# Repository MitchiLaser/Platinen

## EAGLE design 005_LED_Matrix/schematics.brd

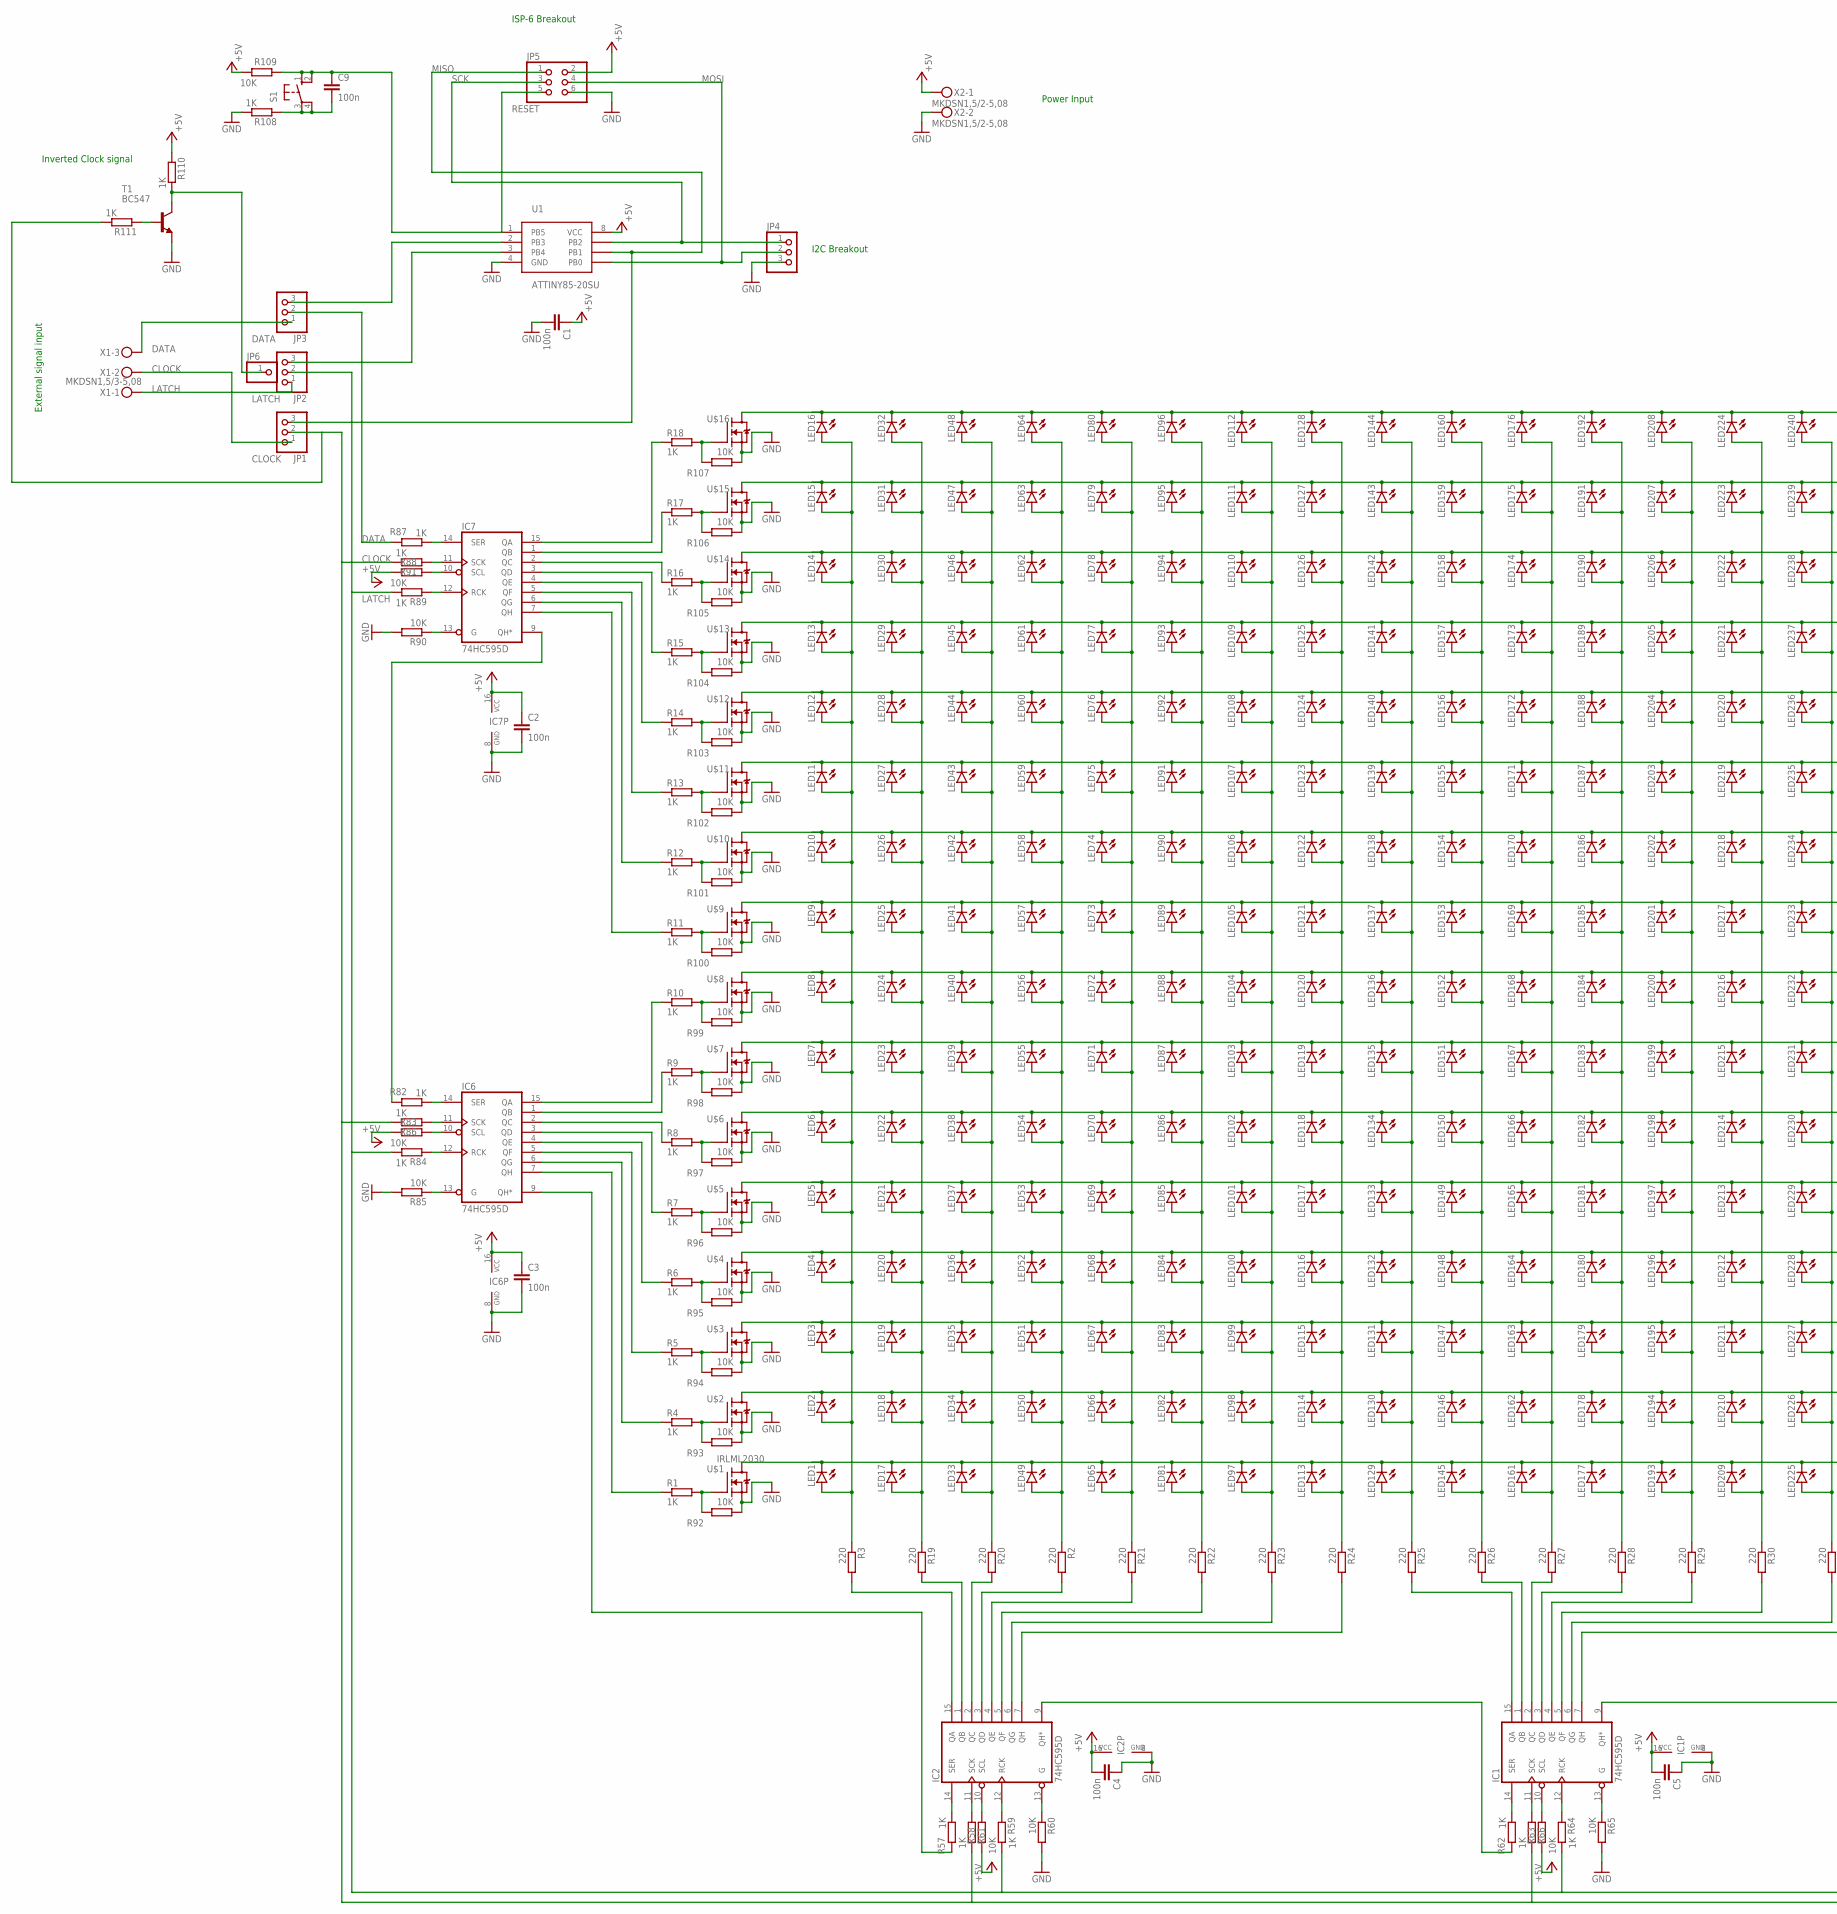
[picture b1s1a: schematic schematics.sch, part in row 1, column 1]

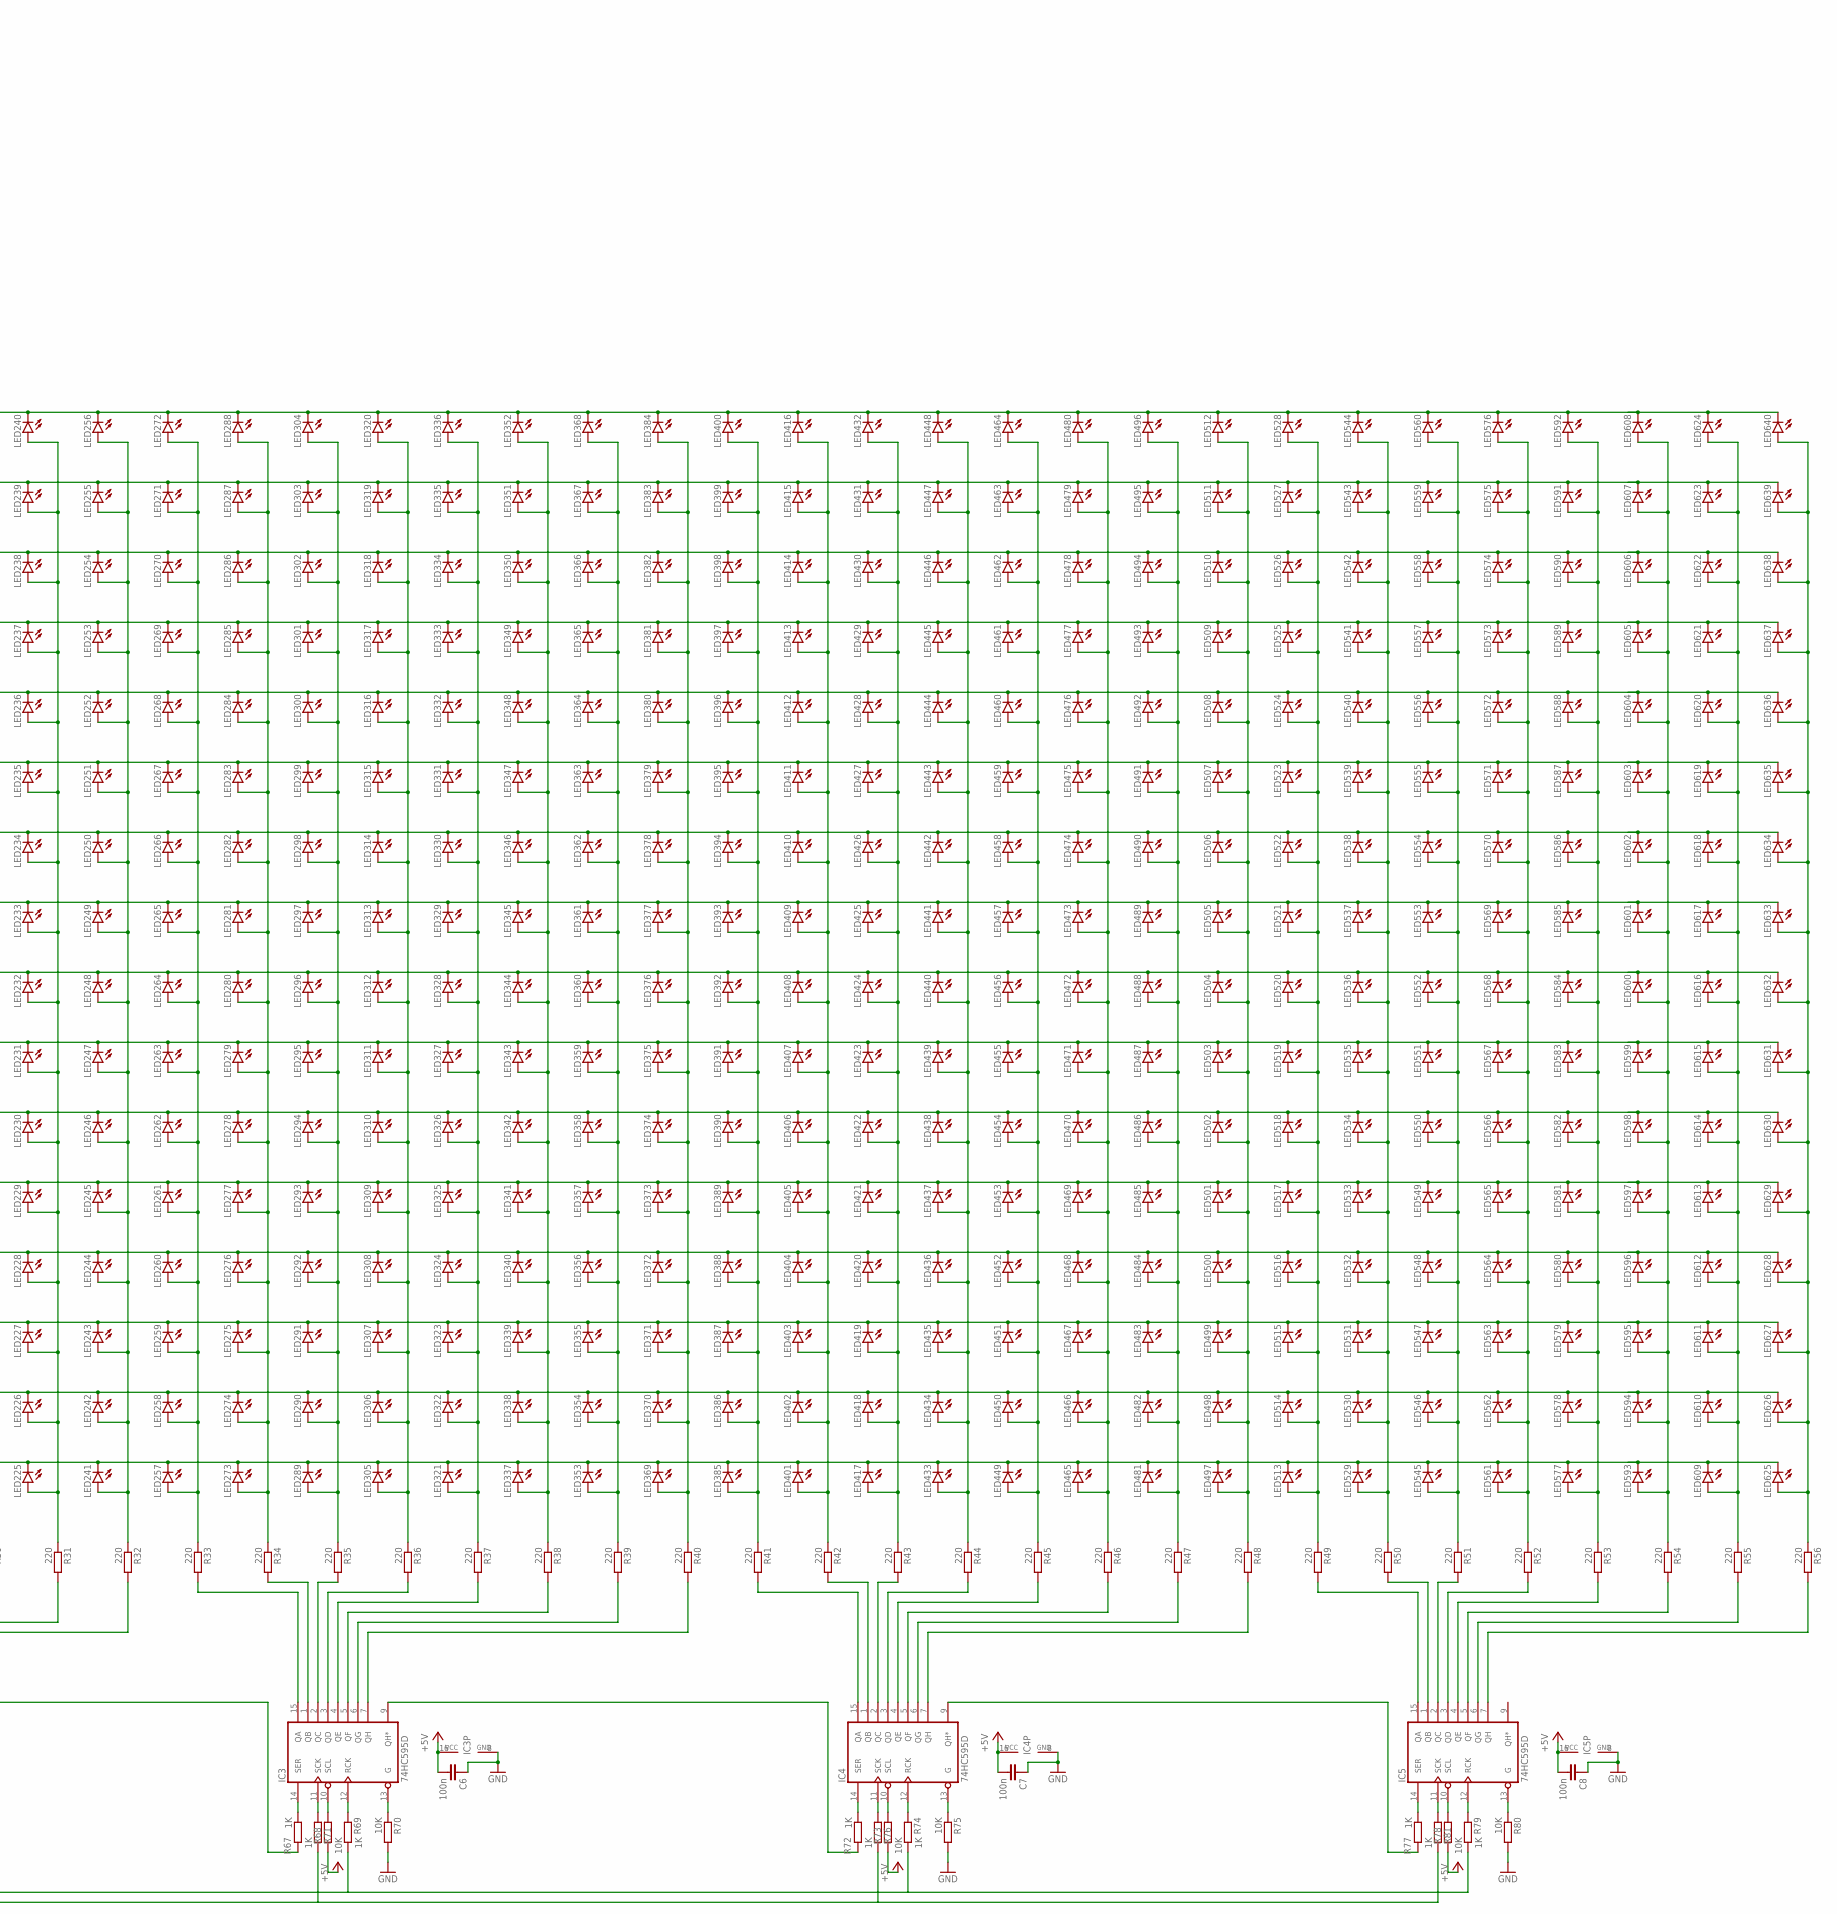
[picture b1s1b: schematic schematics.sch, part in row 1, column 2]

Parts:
C1, C2, C3, C4, C5, C6, C7, C8, C9: 100n; C0805K
IC1, IC2, IC3, IC4, IC5, IC6, IC7: 74HC595D; SO16
JP1, JP2, JP3, JP4: PINHD-1X3; 1X03
JP5: PINHD-2X3; 2X03
JP6: PINHD-1X1; 1X01
LED1, LED2, LED3, LED4, LED5, LED6, LED7, LED8, LED9, LED10, LED11, LED12, LED13, LED14, LED15, LED16, LED17, LED18, LED19, LED20, LED21, LED22, LED23, LED24, LED25, LED26, LED27, LED28, LED29, LED30, LED31, LED32, LED33, LED34, LED35, LED36, LED37, LED38, LED39, LED40, LED41, LED42, LED43, LED44, LED45, LED46, LED47, LED48, LED49, LED50, LED51, LED52, LED53, LED54, LED55, LED56, LED57, LED58, LED59, LED60, LED61, LED62, LED63, LED64, LED65, LED66, LED67, LED68, LED69, LED70, LED71, LED72, LED73, LED74, LED75, LED76, LED77, LED78, LED79, LED80, LED81, LED82, LED83, LED84, LED85, LED86, LED87, LED88, LED89, LED90, LED91, LED92, LED93, LED94, LED95, LED96, LED97, LED98, LED99, LED100, LED101, LED102, LED103, LED104, LED105, LED106, LED107, LED108, LED109, LED110, LED111, LED112, LED113, LED114, LED115, LED116, LED117, LED118, LED119, LED120, LED121, LED122, LED123, LED124, LED125, LED126, LED127, LED128, LED129, LED130, LED131, LED132, LED133, LED134, LED135, LED136, LED137, LED138, LED139, LED140, LED141, LED142, LED143, LED144, LED145, LED146, LED147, LED148, LED149, LED150, LED151, LED152, LED153, LED154, LED155, LED156, LED157, LED158, LED159, LED160, LED161, LED162, LED163, LED164, LED165, LED166, LED167, LED168, LED169, LED170, LED171, LED172, LED173, LED174, LED175, LED176, LED177, LED178, LED179, LED180, LED181, LED182, LED183, LED184, LED185, LED186, LED187, LED188, LED189, LED190, LED191, LED192, LED193, LED194, LED195, LED196, LED197, LED198, LED199, LED200, LED201, LED202, LED203, LED204, LED205, LED206, LED207, LED208, LED209, LED210, LED211, LED212, LED213, LED214, LED215, LED216, LED217, LED218, LED219, LED220, LED221, LED222, LED223, LED224, LED225, LED226, LED227, LED228, LED229, LED230, LED231, LED232, LED233, LED234, LED235, LED236, LED237, LED238, LED239, LED240, LED241, LED242, LED243, LED244, LED245, LED246, LED247, LED248, LED249, LED250, LED251, LED252, LED253, LED254, LED255, LED256, LED257, LED258, LED259, LED260, LED261, LED262, LED263, LED264, LED265, LED266, LED267, LED268, LED269, LED270, LED271, LED272, LED273, LED274, LED275, LED276, LED277, LED278, LED279, LED280, LED281, LED282, LED283, LED284, LED285, LED286, LED287, LED288, LED289, LED290, LED291, LED292, LED293, LED294, LED295, LED296, LED297, LED298, LED299, LED300, LED301, LED302, LED303, LED304, LED305, LED306, LED307, LED308, LED309, LED310, LED311, LED312, LED313, LED314, LED315, LED316, LED317, LED318, LED319, LED320, LED321, LED322, LED323, LED324, LED325, LED326, LED327, LED328, LED329, LED330, LED331, LED332, LED333, LED334, LED335, LED336, LED337, LED338, LED339, LED340, LED341, LED342, LED343, LED344, LED345, LED346, LED347, LED348, LED349, LED350, LED351, LED352, LED353, LED354, LED355, LED356, LED357, LED358, LED359, LED360, LED361, LED362, LED363, LED364, LED365, LED366, LED367, LED368, LED369, LED370, LED371, LED372, LED373, LED374, LED375, LED376, LED377, LED378, LED379, LED380, LED381, LED382, LED383, LED384, LED385, LED386, LED387, LED388, LED389, LED390, LED391, LED392, LED393, LED394, LED395, LED396, LED397, LED398, LED399, LED400, LED401, LED402, LED403, LED404, LED405, LED406, LED407, LED408, LED409, LED410, LED411, LED412, LED413, LED414, LED415, LED416, LED417, LED418, LED419, LED420, LED421, LED422, LED423, LED424, LED425, LED426, LED427, LED428, LED429, LED430, LED431, LED432, LED433, LED434, LED435, LED436, LED437, LED438, LED439, LED440, LED441, LED442, LED443, LED444, LED445, LED446, LED447, LED448, LED449, LED450, LED451, LED452, LED453, LED454, LED455, LED456, LED457, LED458, LED459, LED460, LED461, LED462, LED463, LED464, LED465, LED466, LED467, LED468, LED469, LED470, LED471, LED472, LED473, LED474, LED475, LED476, LED477, LED478, LED479, LED480, LED481, LED482, LED483, LED484, LED485, LED486, LED487, LED488, LED489, LED490, LED491, LED492, LED493, LED494, LED495, LED496, LED497, LED498, LED499, LED500, LED501, LED502, LED503, LED504, LED505, LED506, LED507, LED508, LED509, LED510, LED511, LED512, LED513, LED514, LED515, LED516, LED517, LED518, LED519, LED520, LED521, LED522, LED523, LED524, LED525, LED526, LED527, LED528, LED529, LED530, LED531, LED532, LED533, LED534, LED535, LED536, LED537, LED538, LED539, LED540, LED541, LED542, LED543, LED544, LED545, LED546, LED547, LED548, LED549, LED550, LED551, LED552, LED553, LED554, LED555, LED556, LED557, LED558, LED559, LED560, LED561, LED562, LED563, LED564, LED565, LED566, LED567, LED568, LED569, LED570, LED571, LED572, LED573, LED574, LED575, LED576, LED577, LED578, LED579, LED580, LED581, LED582, LED583, LED584, LED585, LED586, LED587, LED588, LED589, LED590, LED591, LED592, LED593, LED594, LED595, LED596, LED597, LED598, LED599, LED600, LED601, LED602, LED603, LED604, LED605, LED606, LED607, LED608, LED609, LED610, LED611, LED612, LED613, LED614, LED615, LED616, LED617, LED618, LED619, LED620, LED621, LED622, LED623, LED624, LED625, LED626, LED627, LED628, LED629, LED630, LED631, LED632, LED633, LED634, LED635, LED636, LED637, LED638, LED639, LED640: LED3MM
R1, R4, R5, R6, R7, R8, R9, R10, R11, R12, R13, R14, R15, R16, R17, R18, R57, R58, R59, R62, R63, R64, R67, R68, R69, R72, R73, R74, R77, R78, R79, R82, R83, R84, R87, R88, R89, R108, R110, R111: 1K; R0805W
R2, R3, R19, R20, R21, R22, R23, R24, R25, R26, R27, R28, R29, R30, R31, R32, R33, R34, R35, R36, R37, R38, R39, R40, R41, R42, R43, R44, R45, R46, R47, R48, R49, R50, R51, R52, R53, R54, R55, R56: 220; R0805W
R60, R61, R65, R66, R70, R71, R75, R76, R80, R81, R85, R86, R90, R91, R92, R93, R94, R95, R96, R97, R98, R99, R100, R101, R102, R103, R104, R105, R106, R107, R109: 10K; R0805W
S1: 10-XX; B3F-10XX
T1: BC547; TO92
U1: ATTINY85-20SU; SOIC-8
U$1, U$2, U$3, U$4, U$5, U$6, U$7, U$8, U$9, U$10, U$11, U$12, U$13, U$14, U$15, U$16: IRLML2030; SOT23
X1: MKDSN1,5/3-5,08
X2: MKDSN1,5/2-5,08

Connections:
+5V: C1.1, C2.1, C3.1, C4.2, C5.2, C6.2, C7.2, C8.2, IC1.16 (VCC), IC2.16 (VCC), IC3.16 (VCC), IC4.16 (VCC), IC5.16 (VCC), IC6.16 (VCC), IC7.16 (VCC), JP5.2, R61.2, R66.2, R71.2, R76.2, R81.2, R86.2, R91.2, R109.2, R110.1, U1.8 (VCC), X2.1
CLOCK: JP1.2, R58.2, R63.2, R68.2, R73.2, R78.2, R83.2, R88.2, R111.2
DATA: JP3.2, R87.2
GND: C1.2, C2.2, C3.2, C4.1, C5.1, C6.1, C7.1, C8.1, IC1.8 (GND), IC2.8 (GND), IC3.8 (GND), IC4.8 (GND), IC5.8 (GND), IC6.8 (GND), IC7.8 (GND), JP4.3, JP5.6, R60.2, R65.2, R70.2, R75.2, R80.2, R85.2, R90.2, R92.2, R93.2, R94.2, R95.2, R96.2, R97.2, R98.2, R99.2, R100.2, R101.2, R102.2, R103.2, R104.2, R105.2, R106.2, R107.2, R108.2, T1.1 (E), U1.4 (GND), U$1.2 (S), U$2.2 (S), U$3.2 (S), U$4.2 (S), U$5.2 (S), U$6.2 (S), U$7.2 (S), U$8.2 (S), U$9.2 (S), U$10.2 (S), U$11.2 (S), U$12.2 (S), U$13.2 (S), U$14.2 (S), U$15.2 (S), U$16.2 (S), X2.2
LATCH: JP2.2, R59.2, R64.2, R69.2, R74.2, R79.2, R84.2, R89.2
MISO: JP1.3, JP5.1, U1.6 (PB1)
MOSI: JP4.2, JP5.4, U1.5 (PB0)
unnamed: LED1.A, LED2.A, LED3.A, LED4.A, LED5.A, LED6.A, LED7.A, LED8.A, LED9.A, LED10.A, LED11.A, LED12.A, LED13.A, LED14.A, LED15.A, LED16.A, R3.1
unnamed: LED2.K (C), LED18.K (C), LED34.K (C), LED50.K (C), LED66.K (C), LED82.K (C), LED98.K (C), LED114.K (C), LED130.K (C), LED146.K (C), LED162.K (C), LED178.K (C), LED194.K (C), LED210.K (C), LED226.K (C), LED242.K (C), LED258.K (C), LED274.K (C), LED290.K (C), LED306.K (C), LED322.K (C), LED338.K (C), LED354.K (C), LED370.K (C), LED386.K (C), LED402.K (C), LED418.K (C), LED434.K (C), LED450.K (C), LED466.K (C), LED482.K (C), LED498.K (C), LED514.K (C), LED530.K (C), LED546.K (C), LED562.K (C), LED578.K (C), LED594.K (C), LED610.K (C), LED626.K (C), U$2.3 (D)
unnamed: R4.2, R93.1, U$2.1 (G)
unnamed: LED3.K (C), LED19.K (C), LED35.K (C), LED51.K (C), LED67.K (C), LED83.K (C), LED99.K (C), LED115.K (C), LED131.K (C), LED147.K (C), LED163.K (C), LED179.K (C), LED195.K (C), LED211.K (C), LED227.K (C), LED243.K (C), LED259.K (C), LED275.K (C), LED291.K (C), LED307.K (C), LED323.K (C), LED339.K (C), LED355.K (C), LED371.K (C), LED387.K (C), LED403.K (C), LED419.K (C), LED435.K (C), LED451.K (C), LED467.K (C), LED483.K (C), LED499.K (C), LED515.K (C), LED531.K (C), LED547.K (C), LED563.K (C), LED579.K (C), LED595.K (C), LED611.K (C), LED627.K (C), U$3.3 (D)
unnamed: R5.2, R94.1, U$3.1 (G)
unnamed: LED4.K (C), LED20.K (C), LED36.K (C), LED52.K (C), LED68.K (C), LED84.K (C), LED100.K (C), LED116.K (C), LED132.K (C), LED148.K (C), LED164.K (C), LED180.K (C), LED196.K (C), LED212.K (C), LED228.K (C), LED244.K (C), LED260.K (C), LED276.K (C), LED292.K (C), LED308.K (C), LED324.K (C), LED340.K (C), LED356.K (C), LED372.K (C), LED388.K (C), LED404.K (C), LED420.K (C), LED436.K (C), LED452.K (C), LED468.K (C), LED484.K (C), LED500.K (C), LED516.K (C), LED532.K (C), LED548.K (C), LED564.K (C), LED580.K (C), LED596.K (C), LED612.K (C), LED628.K (C), U$4.3 (D)
unnamed: R6.2, R95.1, U$4.1 (G)
unnamed: LED5.K (C), LED21.K (C), LED37.K (C), LED53.K (C), LED69.K (C), LED85.K (C), LED101.K (C), LED117.K (C), LED133.K (C), LED149.K (C), LED165.K (C), LED181.K (C), LED197.K (C), LED213.K (C), LED229.K (C), LED245.K (C), LED261.K (C), LED277.K (C), LED293.K (C), LED309.K (C), LED325.K (C), LED341.K (C), LED357.K (C), LED373.K (C), LED389.K (C), LED405.K (C), LED421.K (C), LED437.K (C), LED453.K (C), LED469.K (C), LED485.K (C), LED501.K (C), LED517.K (C), LED533.K (C), LED549.K (C), LED565.K (C), LED581.K (C), LED597.K (C), LED613.K (C), LED629.K (C), U$5.3 (D)
unnamed: R7.2, R96.1, U$5.1 (G)
unnamed: LED6.K (C), LED22.K (C), LED38.K (C), LED54.K (C), LED70.K (C), LED86.K (C), LED102.K (C), LED118.K (C), LED134.K (C), LED150.K (C), LED166.K (C), LED182.K (C), LED198.K (C), LED214.K (C), LED230.K (C), LED246.K (C), LED262.K (C), LED278.K (C), LED294.K (C), LED310.K (C), LED326.K (C), LED342.K (C), LED358.K (C), LED374.K (C), LED390.K (C), LED406.K (C), LED422.K (C), LED438.K (C), LED454.K (C), LED470.K (C), LED486.K (C), LED502.K (C), LED518.K (C), LED534.K (C), LED550.K (C), LED566.K (C), LED582.K (C), LED598.K (C), LED614.K (C), LED630.K (C), U$6.3 (D)
unnamed: R8.2, R97.1, U$6.1 (G)
unnamed: LED7.K (C), LED23.K (C), LED39.K (C), LED55.K (C), LED71.K (C), LED87.K (C), LED103.K (C), LED119.K (C), LED135.K (C), LED151.K (C), LED167.K (C), LED183.K (C), LED199.K (C), LED215.K (C), LED231.K (C), LED247.K (C), LED263.K (C), LED279.K (C), LED295.K (C), LED311.K (C), LED327.K (C), LED343.K (C), LED359.K (C), LED375.K (C), LED391.K (C), LED407.K (C), LED423.K (C), LED439.K (C), LED455.K (C), LED471.K (C), LED487.K (C), LED503.K (C), LED519.K (C), LED535.K (C), LED551.K (C), LED567.K (C), LED583.K (C), LED599.K (C), LED615.K (C), LED631.K (C), U$7.3 (D)
unnamed: R9.2, R98.1, U$7.1 (G)
unnamed: LED8.K (C), LED24.K (C), LED40.K (C), LED56.K (C), LED72.K (C), LED88.K (C), LED104.K (C), LED120.K (C), LED136.K (C), LED152.K (C), LED168.K (C), LED184.K (C), LED200.K (C), LED216.K (C), LED232.K (C), LED248.K (C), LED264.K (C), LED280.K (C), LED296.K (C), LED312.K (C), LED328.K (C), LED344.K (C), LED360.K (C), LED376.K (C), LED392.K (C), LED408.K (C), LED424.K (C), LED440.K (C), LED456.K (C), LED472.K (C), LED488.K (C), LED504.K (C), LED520.K (C), LED536.K (C), LED552.K (C), LED568.K (C), LED584.K (C), LED600.K (C), LED616.K (C), LED632.K (C), U$8.3 (D)
unnamed: R10.2, R99.1, U$8.1 (G)
unnamed: LED1.K (C), LED17.K (C), LED33.K (C), LED49.K (C), LED65.K (C), LED81.K (C), LED97.K (C), LED113.K (C), LED129.K (C), LED145.K (C), LED161.K (C), LED177.K (C), LED193.K (C), LED209.K (C), LED225.K (C), LED241.K (C), LED257.K (C), LED273.K (C), LED289.K (C), LED305.K (C), LED321.K (C), LED337.K (C), LED353.K (C), LED369.K (C), LED385.K (C), LED401.K (C), LED417.K (C), LED433.K (C), LED449.K (C), LED465.K (C), LED481.K (C), LED497.K (C), LED513.K (C), LED529.K (C), LED545.K (C), LED561.K (C), LED577.K (C), LED593.K (C), LED609.K (C), LED625.K (C), U$1.3 (D)
unnamed: R1.2, R92.1, U$1.1 (G)
unnamed: LED9.K (C), LED25.K (C), LED41.K (C), LED57.K (C), LED73.K (C), LED89.K (C), LED105.K (C), LED121.K (C), LED137.K (C), LED153.K (C), LED169.K (C), LED185.K (C), LED201.K (C), LED217.K (C), LED233.K (C), LED249.K (C), LED265.K (C), LED281.K (C), LED297.K (C), LED313.K (C), LED329.K (C), LED345.K (C), LED361.K (C), LED377.K (C), LED393.K (C), LED409.K (C), LED425.K (C), LED441.K (C), LED457.K (C), LED473.K (C), LED489.K (C), LED505.K (C), LED521.K (C), LED537.K (C), LED553.K (C), LED569.K (C), LED585.K (C), LED601.K (C), LED617.K (C), LED633.K (C), U$9.3 (D)
unnamed: R11.2, R100.1, U$9.1 (G)
unnamed: LED10.K (C), LED26.K (C), LED42.K (C), LED58.K (C), LED74.K (C), LED90.K (C), LED106.K (C), LED122.K (C), LED138.K (C), LED154.K (C), LED170.K (C), LED186.K (C), LED202.K (C), LED218.K (C), LED234.K (C), LED250.K (C), LED266.K (C), LED282.K (C), LED298.K (C), LED314.K (C), LED330.K (C), LED346.K (C), LED362.K (C), LED378.K (C), LED394.K (C), LED410.K (C), LED426.K (C), LED442.K (C), LED458.K (C), LED474.K (C), LED490.K (C), LED506.K (C), LED522.K (C), LED538.K (C), LED554.K (C), LED570.K (C), LED586.K (C), LED602.K (C), LED618.K (C), LED634.K (C), U$10.3 (D)
unnamed: R12.2, R101.1, U$10.1 (G)
unnamed: LED11.K (C), LED27.K (C), LED43.K (C), LED59.K (C), LED75.K (C), LED91.K (C), LED107.K (C), LED123.K (C), LED139.K (C), LED155.K (C), LED171.K (C), LED187.K (C), LED203.K (C), LED219.K (C), LED235.K (C), LED251.K (C), LED267.K (C), LED283.K (C), LED299.K (C), LED315.K (C), LED331.K (C), LED347.K (C), LED363.K (C), LED379.K (C), LED395.K (C), LED411.K (C), LED427.K (C), LED443.K (C), LED459.K (C), LED475.K (C), LED491.K (C), LED507.K (C), LED523.K (C), LED539.K (C), LED555.K (C), LED571.K (C), LED587.K (C), LED603.K (C), LED619.K (C), LED635.K (C), U$11.3 (D)
unnamed: R13.2, R102.1, U$11.1 (G)
unnamed: LED12.K (C), LED28.K (C), LED44.K (C), LED60.K (C), LED76.K (C), LED92.K (C), LED108.K (C), LED124.K (C), LED140.K (C), LED156.K (C), LED172.K (C), LED188.K (C), LED204.K (C), LED220.K (C), LED236.K (C), LED252.K (C), LED268.K (C), LED284.K (C), LED300.K (C), LED316.K (C), LED332.K (C), LED348.K (C), LED364.K (C), LED380.K (C), LED396.K (C), LED412.K (C), LED428.K (C), LED444.K (C), LED460.K (C), LED476.K (C), LED492.K (C), LED508.K (C), LED524.K (C), LED540.K (C), LED556.K (C), LED572.K (C), LED588.K (C), LED604.K (C), LED620.K (C), LED636.K (C), U$12.3 (D)
unnamed: R14.2, R103.1, U$12.1 (G)
unnamed: LED13.K (C), LED29.K (C), LED45.K (C), LED61.K (C), LED77.K (C), LED93.K (C), LED109.K (C), LED125.K (C), LED141.K (C), LED157.K (C), LED173.K (C), LED189.K (C), LED205.K (C), LED221.K (C), LED237.K (C), LED253.K (C), LED269.K (C), LED285.K (C), LED301.K (C), LED317.K (C), LED333.K (C), LED349.K (C), LED365.K (C), LED381.K (C), LED397.K (C), LED413.K (C), LED429.K (C), LED445.K (C), LED461.K (C), LED477.K (C), LED493.K (C), LED509.K (C), LED525.K (C), LED541.K (C), LED557.K (C), LED573.K (C), LED589.K (C), LED605.K (C), LED621.K (C), LED637.K (C), U$13.3 (D)
unnamed: R15.2, R104.1, U$13.1 (G)
unnamed: LED14.K (C), LED30.K (C), LED46.K (C), LED62.K (C), LED78.K (C), LED94.K (C), LED110.K (C), LED126.K (C), LED142.K (C), LED158.K (C), LED174.K (C), LED190.K (C), LED206.K (C), LED222.K (C), LED238.K (C), LED254.K (C), LED270.K (C), LED286.K (C), LED302.K (C), LED318.K (C), LED334.K (C), LED350.K (C), LED366.K (C), LED382.K (C), LED398.K (C), LED414.K (C), LED430.K (C), LED446.K (C), LED462.K (C), LED478.K (C), LED494.K (C), LED510.K (C), LED526.K (C), LED542.K (C), LED558.K (C), LED574.K (C), LED590.K (C), LED606.K (C), LED622.K (C), LED638.K (C), U$14.3 (D)
unnamed: R16.2, R105.1, U$14.1 (G)
unnamed: LED15.K (C), LED31.K (C), LED47.K (C), LED63.K (C), LED79.K (C), LED95.K (C), LED111.K (C), LED127.K (C), LED143.K (C), LED159.K (C), LED175.K (C), LED191.K (C), LED207.K (C), LED223.K (C), LED239.K (C), LED255.K (C), LED271.K (C), LED287.K (C), LED303.K (C), LED319.K (C), LED335.K (C), LED351.K (C), LED367.K (C), LED383.K (C), LED399.K (C), LED415.K (C), LED431.K (C), LED447.K (C), LED463.K (C), LED479.K (C), LED495.K (C), LED511.K (C), LED527.K (C), LED543.K (C), LED559.K (C), LED575.K (C), LED591.K (C), LED607.K (C), LED623.K (C), LED639.K (C), U$15.3 (D)
unnamed: R17.2, R106.1, U$15.1 (G)
unnamed: LED16.K (C), LED32.K (C), LED48.K (C), LED64.K (C), LED80.K (C), LED96.K (C), LED112.K (C), LED128.K (C), LED144.K (C), LED160.K (C), LED176.K (C), LED192.K (C), LED208.K (C), LED224.K (C), LED240.K (C), LED256.K (C), LED272.K (C), LED288.K (C), LED304.K (C), LED320.K (C), LED336.K (C), LED352.K (C), LED368.K (C), LED384.K (C), LED400.K (C), LED416.K (C), LED432.K (C), LED448.K (C), LED464.K (C), LED480.K (C), LED496.K (C), LED512.K (C), LED528.K (C), LED544.K (C), LED560.K (C), LED576.K (C), LED592.K (C), LED608.K (C), LED624.K (C), LED640.K (C), U$16.3 (D)
unnamed: R18.2, R107.1, U$16.1 (G)
unnamed: LED17.A, LED18.A, LED19.A, LED20.A, LED21.A, LED22.A, LED23.A, LED24.A, LED25.A, LED26.A, LED27.A, LED28.A, LED29.A, LED30.A, LED31.A, LED32.A, R19.1
unnamed: IC2.14 (SER), R57.1
unnamed: IC2.11 (SCK), R58.1
unnamed: IC2.12 (RCK), R59.1
unnamed: IC2.13 (G), R60.1
unnamed: IC2.10 (SCL), R61.1
unnamed: IC2.1 (QB), R19.2
unnamed: IC2.15 (QA), R3.2
unnamed: IC2.2 (QC), R20.2
unnamed: IC2.3 (QD), R2.2
unnamed: IC2.4 (QE), R21.2
unnamed: IC2.5 (QF), R22.2
unnamed: IC2.6 (QG), R23.2
unnamed: IC2.7 (QH), R24.2
unnamed: IC1.14 (SER), R62.1
unnamed: IC1.11 (SCK), R63.1
unnamed: IC1.12 (RCK), R64.1
unnamed: LED33.A, LED34.A, LED35.A, LED36.A, LED37.A, LED38.A, LED39.A, LED40.A, LED41.A, LED42.A, LED43.A, LED44.A, LED45.A, LED46.A, LED47.A, LED48.A, R20.1
unnamed: LED49.A, LED50.A, LED51.A, LED52.A, LED53.A, LED54.A, LED55.A, LED56.A, LED57.A, LED58.A, LED59.A, LED60.A, LED61.A, LED62.A, LED63.A, LED64.A, R2.1
unnamed: LED65.A, LED66.A, LED67.A, LED68.A, LED69.A, LED70.A, LED71.A, LED72.A, LED73.A, LED74.A, LED75.A, LED76.A, LED77.A, LED78.A, LED79.A, LED80.A, R21.1
unnamed: LED81.A, LED82.A, LED83.A, LED84.A, LED85.A, LED86.A, LED87.A, LED88.A, LED89.A, LED90.A, LED91.A, LED92.A, LED93.A, LED94.A, LED95.A, LED96.A, R22.1
unnamed: LED97.A, LED98.A, LED99.A, LED100.A, LED101.A, LED102.A, LED103.A, LED104.A, LED105.A, LED106.A, LED107.A, LED108.A, LED109.A, LED110.A, LED111.A, LED112.A, R23.1
unnamed: LED113.A, LED114.A, LED115.A, LED116.A, LED117.A, LED118.A, LED119.A, LED120.A, LED121.A, LED122.A, LED123.A, LED124.A, LED125.A, LED126.A, LED127.A, LED128.A, R24.1
unnamed: LED129.A, LED130.A, LED131.A, LED132.A, LED133.A, LED134.A, LED135.A, LED136.A, LED137.A, LED138.A, LED139.A, LED140.A, LED141.A, LED142.A, LED143.A, LED144.A, R25.1
unnamed: LED145.A, LED146.A, LED147.A, LED148.A, LED149.A, LED150.A, LED151.A, LED152.A, LED153.A, LED154.A, LED155.A, LED156.A, LED157.A, LED158.A, LED159.A, LED160.A, R26.1
unnamed: LED161.A, LED162.A, LED163.A, LED164.A, LED165.A, LED166.A, LED167.A, LED168.A, LED169.A, LED170.A, LED171.A, LED172.A, LED173.A, LED174.A, LED175.A, LED176.A, R27.1
unnamed: LED177.A, LED178.A, LED179.A, LED180.A, LED181.A, LED182.A, LED183.A, LED184.A, LED185.A, LED186.A, LED187.A, LED188.A, LED189.A, LED190.A, LED191.A, LED192.A, R28.1
unnamed: LED193.A, LED194.A, LED195.A, LED196.A, LED197.A, LED198.A, LED199.A, LED200.A, LED201.A, LED202.A, LED203.A, LED204.A, LED205.A, LED206.A, LED207.A, LED208.A, R29.1
unnamed: LED209.A, LED210.A, LED211.A, LED212.A, LED213.A, LED214.A, LED215.A, LED216.A, LED217.A, LED218.A, LED219.A, LED220.A, LED221.A, LED222.A, LED223.A, LED224.A, R30.1
unnamed: LED225.A, LED226.A, LED227.A, LED228.A, LED229.A, LED230.A, LED231.A, LED232.A, LED233.A, LED234.A, LED235.A, LED236.A, LED237.A, LED238.A, LED239.A, LED240.A, R31.1
unnamed: LED241.A, LED242.A, LED243.A, LED244.A, LED245.A, LED246.A, LED247.A, LED248.A, LED249.A, LED250.A, LED251.A, LED252.A, LED253.A, LED254.A, LED255.A, LED256.A, R32.1
unnamed: LED257.A, LED258.A, LED259.A, LED260.A, LED261.A, LED262.A, LED263.A, LED264.A, LED265.A, LED266.A, LED267.A, LED268.A, LED269.A, LED270.A, LED271.A, LED272.A, R33.1
unnamed: LED273.A, LED274.A, LED275.A, LED276.A, LED277.A, LED278.A, LED279.A, LED280.A, LED281.A, LED282.A, LED283.A, LED284.A, LED285.A, LED286.A, LED287.A, LED288.A, R34.1
unnamed: LED289.A, LED290.A, LED291.A, LED292.A, LED293.A, LED294.A, LED295.A, LED296.A, LED297.A, LED298.A, LED299.A, LED300.A, LED301.A, LED302.A, LED303.A, LED304.A, R35.1
unnamed: LED305.A, LED306.A, LED307.A, LED308.A, LED309.A, LED310.A, LED311.A, LED312.A, LED313.A, LED314.A, LED315.A, LED316.A, LED317.A, LED318.A, LED319.A, LED320.A, R36.1
unnamed: LED321.A, LED322.A, LED323.A, LED324.A, LED325.A, LED326.A, LED327.A, LED328.A, LED329.A, LED330.A, LED331.A, LED332.A, LED333.A, LED334.A, LED335.A, LED336.A, R37.1
unnamed: LED337.A, LED338.A, LED339.A, LED340.A, LED341.A, LED342.A, LED343.A, LED344.A, LED345.A, LED346.A, LED347.A, LED348.A, LED349.A, LED350.A, LED351.A, LED352.A, R38.1
unnamed: LED401.A, LED402.A, LED403.A, LED404.A, LED405.A, LED406.A, LED407.A, LED408.A, LED409.A, LED410.A, LED411.A, LED412.A, LED413.A, LED414.A, LED415.A, LED416.A, R42.1
unnamed: LED481.A, LED482.A, LED483.A, LED484.A, LED485.A, LED486.A, LED487.A, LED488.A, LED489.A, LED490.A, LED491.A, LED492.A, LED493.A, LED494.A, LED495.A, LED496.A, R47.1
unnamed: IC1.13 (G), R65.1
unnamed: IC1.10 (SCL), R66.1
unnamed: IC1.2 (QC), R27.2
unnamed: IC1.3 (QD), R28.2
unnamed: IC1.4 (QE), R29.2
unnamed: IC1.5 (QF), R30.2
unnamed: IC1.6 (QG), R31.2
unnamed: IC1.7 (QH), R32.2
unnamed: IC1.1 (QB), R26.2
unnamed: IC1.15 (QA), R25.2
unnamed: IC3.14 (SER), R67.1
unnamed: IC3.11 (SCK), R68.1
unnamed: IC3.12 (RCK), R69.1
unnamed: IC3.13 (G), R70.1
unnamed: LED353.A, LED354.A, LED355.A, LED356.A, LED357.A, LED358.A, LED359.A, LED360.A, LED361.A, LED362.A, LED363.A, LED364.A, LED365.A, LED366.A, LED367.A, LED368.A, R39.1
unnamed: IC3.10 (SCL), R71.1
unnamed: LED417.A, LED418.A, LED419.A, LED420.A, LED421.A, LED422.A, LED423.A, LED424.A, LED425.A, LED426.A, LED427.A, LED428.A, LED429.A, LED430.A, LED431.A, LED432.A, R43.1
unnamed: IC3.2 (QC), R35.2
unnamed: LED497.A, LED498.A, LED499.A, LED500.A, LED501.A, LED502.A, LED503.A, LED504.A, LED505.A, LED506.A, LED507.A, LED508.A, LED509.A, LED510.A, LED511.A, LED512.A, R48.1
unnamed: IC3.3 (QD), R36.2
unnamed: IC3.4 (QE), R37.2
unnamed: IC3.5 (QF), R38.2
unnamed: IC3.6 (QG), R39.2
unnamed: IC3.7 (QH), R40.2
unnamed: IC3.1 (QB), R34.2
unnamed: IC3.15 (QA), R33.2
unnamed: IC4.14 (SER), R72.1
unnamed: IC4.11 (SCK), R73.1
unnamed: IC4.12 (RCK), R74.1
unnamed: IC4.13 (G), R75.1
unnamed: IC4.10 (SCL), R76.1
unnamed: LED369.A, LED370.A, LED371.A, LED372.A, LED373.A, LED374.A, LED375.A, LED376.A, LED377.A, LED378.A, LED379.A, LED380.A, LED381.A, LED382.A, LED383.A, LED384.A, R40.1
unnamed: IC4.2 (QC), R43.2
unnamed: IC4.3 (QD), R44.2
unnamed: LED433.A, LED434.A, LED435.A, LED436.A, LED437.A, LED438.A, LED439.A, LED440.A, LED441.A, LED442.A, LED443.A, LED444.A, LED445.A, LED446.A, LED447.A, LED448.A, R44.1
unnamed: IC4.4 (QE), R45.2
unnamed: IC4.5 (QF), R46.2
unnamed: LED513.A, LED514.A, LED515.A, LED516.A, LED517.A, LED518.A, LED519.A, LED520.A, LED521.A, LED522.A, LED523.A, LED524.A, LED525.A, LED526.A, LED527.A, LED528.A, R49.1
unnamed: IC4.6 (QG), R47.2
unnamed: IC4.7 (QH), R48.2
unnamed: IC4.1 (QB), R42.2
unnamed: IC4.15 (QA), R41.2
unnamed: IC5.14 (SER), R77.1
unnamed: IC5.11 (SCK), R78.1
unnamed: IC5.12 (RCK), R79.1
unnamed: IC5.13 (G), R80.1
unnamed: IC5.10 (SCL), R81.1
unnamed: IC5.2 (QC), R51.2
unnamed: LED385.A, LED386.A, LED387.A, LED388.A, LED389.A, LED390.A, LED391.A, LED392.A, LED393.A, LED394.A, LED395.A, LED396.A, LED397.A, LED398.A, LED399.A, LED400.A, R41.1
unnamed: IC5.3 (QD), R52.2
unnamed: IC5.4 (QE), R53.2
unnamed: IC5.5 (QF), R54.2
unnamed: LED449.A, LED450.A, LED451.A, LED452.A, LED453.A, LED454.A, LED455.A, LED456.A, LED457.A, LED458.A, LED459.A, LED460.A, LED461.A, LED462.A, LED463.A, LED464.A, R45.1
unnamed: IC5.6 (QG), R55.2
unnamed: IC5.7 (QH), R56.2
unnamed: IC5.1 (QB), R50.2
unnamed: LED529.A, LED530.A, LED531.A, LED532.A, LED533.A, LED534.A, LED535.A, LED536.A, LED537.A, LED538.A, LED539.A, LED540.A, LED541.A, LED542.A, LED543.A, LED544.A, R50.1
unnamed: IC5.15 (QA), R49.2
unnamed: IC6.14 (SER), R82.1
unnamed: IC6.11 (SCK), R83.1
unnamed: IC6.12 (RCK), R84.1
unnamed: IC6.13 (G), R85.1
unnamed: IC6.10 (SCL), R86.1
unnamed: IC6.2 (QC), R8.1
unnamed: IC6.3 (QD), R7.1
unnamed: IC6.4 (QE), R6.1
unnamed: IC6.5 (QF), R5.1
unnamed: IC6.6 (QG), R4.1
unnamed: IC6.7 (QH), R1.1
unnamed: LED465.A, LED466.A, LED467.A, LED468.A, LED469.A, LED470.A, LED471.A, LED472.A, LED473.A, LED474.A, LED475.A, LED476.A, LED477.A, LED478.A, LED479.A, LED480.A, R46.1
unnamed: IC6.1 (QB), R9.1
unnamed: IC6.15 (QA), R10.1
unnamed: IC7.14 (SER), R87.1
unnamed: IC7.11 (SCK), R88.1
unnamed: LED545.A, LED546.A, LED547.A, LED548.A, LED549.A, LED550.A, LED551.A, LED552.A, LED553.A, LED554.A, LED555.A, LED556.A, LED557.A, LED558.A, LED559.A, LED560.A, R51.1
unnamed: IC7.12 (RCK), R89.1
unnamed: IC7.13 (G), R90.1
unnamed: IC7.10 (SCL), R91.1
unnamed: IC7.2 (QC), R16.1
unnamed: IC7.3 (QD), R15.1
unnamed: IC7.4 (QE), R14.1
unnamed: IC7.5 (QF), R13.1
unnamed: IC7.6 (QG), R12.1
unnamed: IC7.7 (QH), R11.1
unnamed: IC7.1 (QB), R17.1
unnamed: IC7.15 (QA), R18.1
unnamed: IC1.9 (QH*), R67.2
unnamed: IC3.9 (QH*), R72.2
unnamed: IC4.9 (QH*), R77.2
unnamed: IC2.9 (QH*), R62.2
unnamed: IC7.9 (QH*), R82.2
unnamed: LED561.A, LED562.A, LED563.A, LED564.A, LED565.A, LED566.A, LED567.A, LED568.A, LED569.A, LED570.A, LED571.A, LED572.A, LED573.A, LED574.A, LED575.A, LED576.A, R52.1
unnamed: IC6.9 (QH*), R57.2
unnamed: JP6.1, R110.2, T1.3 (C)
unnamed: C9.2, R108.1, S1.3, S1.4 (P1)
unnamed: JP3.1, X1.3
unnamed: JP1.1, X1.2
unnamed: JP2.1, X1.1
unnamed: R111.1, T1.2 (B)
unnamed: JP2.3, U1.3 (PB4)
unnamed: JP3.3, U1.2 (PB3)
unnamed: LED577.A, LED578.A, LED579.A, LED580.A, LED581.A, LED582.A, LED583.A, LED584.A, LED585.A, LED586.A, LED587.A, LED588.A, LED589.A, LED590.A, LED591.A, LED592.A, R53.1
unnamed: LED593.A, LED594.A, LED595.A, LED596.A, LED597.A, LED598.A, LED599.A, LED600.A, LED601.A, LED602.A, LED603.A, LED604.A, LED605.A, LED606.A, LED607.A, LED608.A, R54.1
unnamed: LED609.A, LED610.A, LED611.A, LED612.A, LED613.A, LED614.A, LED615.A, LED616.A, LED617.A, LED618.A, LED619.A, LED620.A, LED621.A, LED622.A, LED623.A, LED624.A, R55.1
unnamed: LED625.A, LED626.A, LED627.A, LED628.A, LED629.A, LED630.A, LED631.A, LED632.A, LED633.A, LED634.A, LED635.A, LED636.A, LED637.A, LED638.A, LED639.A, LED640.A, R56.1
RESET: C9.1, JP5.5, R109.1, S1.1 (S), S1.2 (S1), U1.1 (PB5)
SCK: JP4.1, JP5.3, U1.7 (PB2)

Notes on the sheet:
I2C Breakout
Power Input
ISP-6 Breakout
External signal input
Inverted Clock signal

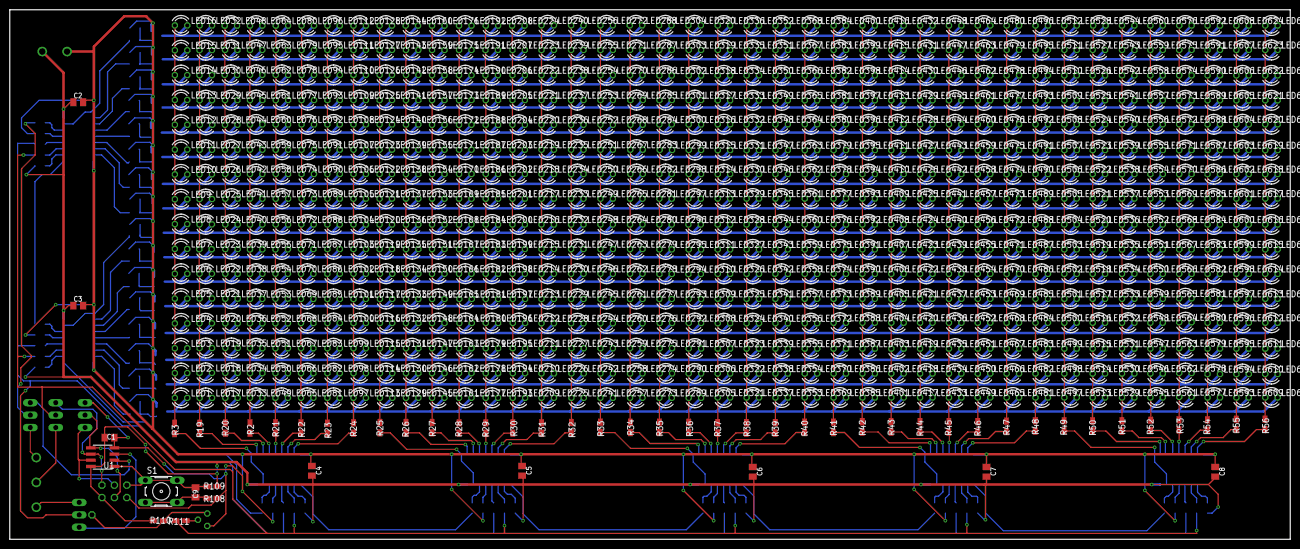
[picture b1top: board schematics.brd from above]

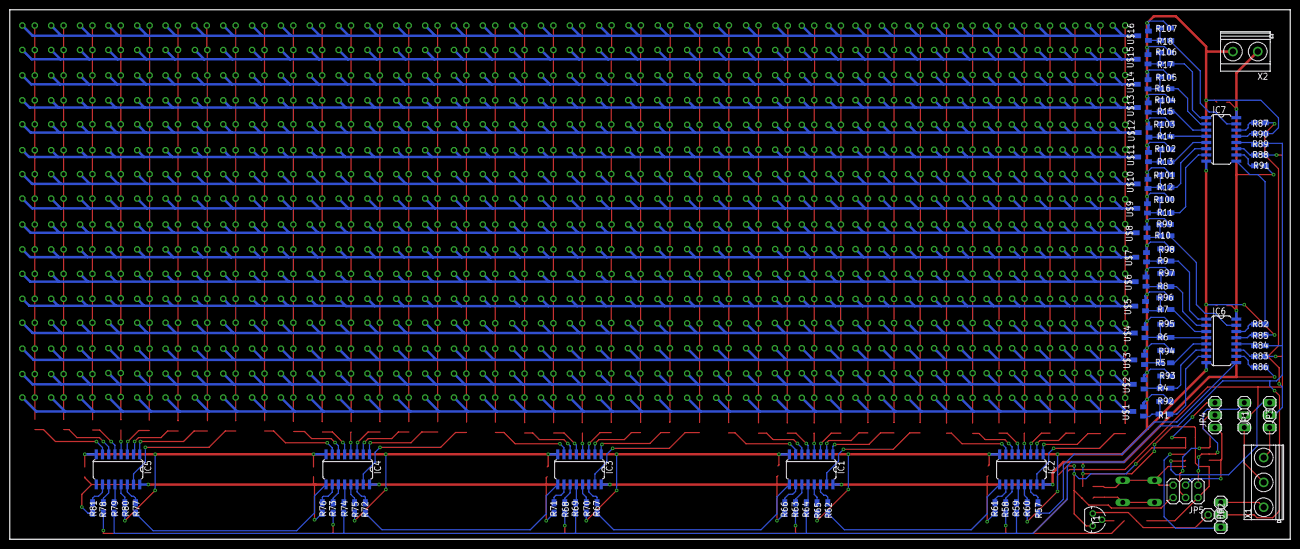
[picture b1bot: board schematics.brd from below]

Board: 2 copper layers, 261.9 x 108.3 mm, 794 parts (99 on the bottom side), 186 nets.
